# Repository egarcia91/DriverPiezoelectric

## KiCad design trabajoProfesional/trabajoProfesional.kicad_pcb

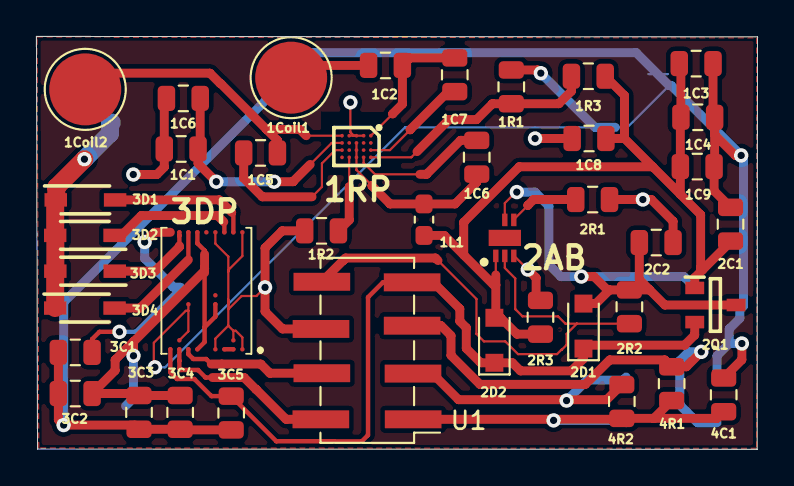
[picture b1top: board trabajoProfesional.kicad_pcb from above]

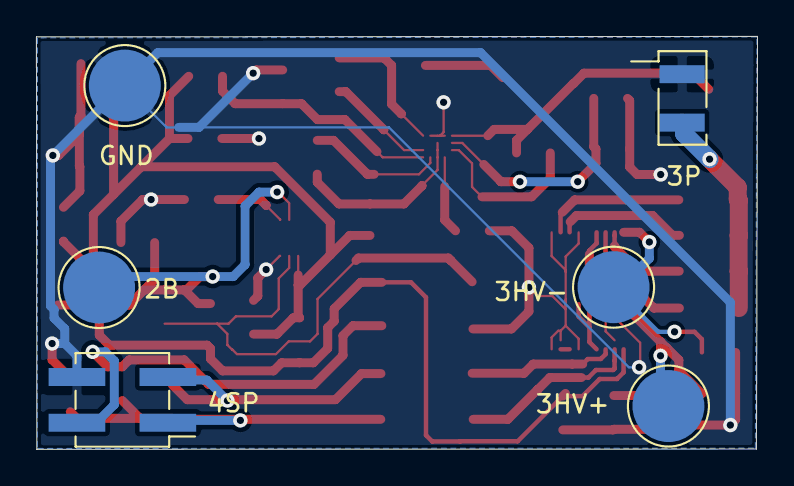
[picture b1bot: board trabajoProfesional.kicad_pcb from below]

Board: 2 copper layers, 40.1 x 22.9 mm, 46 parts (6 on the bottom side), 29 nets.

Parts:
1C1, 1C3, 1C4, 1C8, 1C9: 22u; C_0805_2012Metric
1C2: 10n; C_0805_2012Metric
1C5, 1C7: 1n; C_0805_2012Metric
1C6, 4C1: 100n; C_0805_2012Metric
1C6#2: 47n; C_0805_2012Metric
1Coil1, 1Coil2, 2B, 3HV+, 3HV-: Conn_01x01_Male; TestPoint_Pad_D4.0mm
1L1: 4.7u; L_0603_1608Metric_Pad1.05x0.95mm_HandSolder
1R1, 2R1, 2R2, 4R1, 4R2: 10k; R_0805_2012Metric
1R2: 60k; R_0805_2012Metric
1R3: 46k; R_0805_2012Metric
1RP: TS51223-M000WCSR; BGA20C40P4X5_190X230X58
2AB: SC810ULTRT; SON50P200X200X60-7N-D
2C1, 2C2: 2.2u; C_0805_2012Metric
2D1, 2D2: D_Schottky; D_SOD-323_HandSoldering
2Q1: BSS84; SOT95P240X120-3N
2R3: R; R_0805_2012Metric
3C1: 4.7; C_0805_2012Metric
3C2, 3C3, 3C4, 3C5: 4.7u; C_0805_2012Metric
3D1, 3D2, 3D3, 3D4: 1N4150W-E3-08; SOD3716X135N
3DP: HV7360GA-G; HV7360GAG
3P: UTR-1440K-TT-R; PinHeader_1x02_P2.54mm_Vertical_SMD_Pin1Left
4SP: MS583730BA01-50; PinHeader_2x02_P2.54mm_Vertical_SMD
GND: Conn_01x01_Male; TestPoint_Pad_D4.0mm
U1: 1501; PinHeader_2x04_P2.54mm_Vertical_SMD

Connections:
+Bat: 2AB.5, 2B.1, 2C2.1, 2D1.2, 2Q1.3, 2R2.1
+HV: 3C2.2, 3C3.2, 3C4.1, 3DP.A6, 3DP.F4, 3DP.P6, 3HV+.1
-HV: 3C1.2, 3DP.P9, 3HV-.1
/Bateria/Cargando: 2AB.2, 2R2.2, U1.8
/Salida/Alimentacion: 2D1.1, 2D2.1, 2Q1.2, 3C5.1, 3DP.A9, U1.1
/Salida/SN1ONOFF: 3DP.A7, U1.4
/Salida/SP1ONOFF: 3DP.A8, U1.3
GND: 1C1.1, 1C3.1, 1C4.1, 1C6.1, 1C8.1, 1C9.1, 1R1.1, 1R2.2, 1RP.B1, 1RP.C1, 1RP.D1, 2AB.3, 2C1.2, 2C2.2, 2R1.1, 2R3.1, 3C1.1, 3C2.1, 3C3.1, 3C4.2, 3C5.2, 3DP.A1, 3DP.A4, 3DP.B2, 3DP.B8, 3DP.F7, 3DP.P1, 3DP.P4, 3P.1, 4C1.1, 4SP.4, GND.1, U1.2
unnamed: 1C3.2, 1C4.2, 1C8.2, 1C9.2, 1L1.1, 1R3.1, 2AB.1, 2C1.1, 2D2.2, 2Q1.1, 2R3.2
unnamed: 2AB.4, 2R1.2
unnamed: 4C1.2, 4R1.1, 4R2.1, 4SP.1, U1.6
unnamed: 1C6#2.1, 1L1.2, 1RP.C2, 1RP.C3, 1RP.C4
unnamed: 1C6#2.2, 1RP.B4
unnamed: 1C5.1, 1RP.E3
unnamed: 1C5.2, 1Coil2.1, 1RP.E1
unnamed: 1C2.1, 1C7.1, 1RP.A1
unnamed: 1C7.2, 1RP.A3
unnamed: 1C1.2, 1C6.2, 1RP.E2
unnamed: 1C2.2, 1Coil1.1
unnamed: 3D3.1, 3DP.P8
unnamed: 3D1.1, 3D2.2, 3D3.2, 3D4.1, 3P.2
unnamed: 3D2.1, 3DP.P3
unnamed: 3D1.2, 3DP.P2
unnamed: 3D4.2, 3DP.P7
unnamed: 3DP.A2, 3DP.A3
unnamed: 1R1.2, 1R3.2, 1RP.A4
unnamed: 1R2.1, 1RP.D4
SCLPresion: 4R2.2, 4SP.3, U1.7
SDAPresion: 4R1.2, 4SP.2, U1.5

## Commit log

2020-04-02 comeinza elesquematico
2020-07-06 Se crea el primer intento de placa para el integrado dificil de soldar
2020-07-13 ahora se modifico la via para que quede lo mas grande posible y fuera del pin VGA
2020-08-16 va el parche con el ultimo mod del los pines anulados
2020-08-16 se agregan todos los componentes al squematico
2020-08-16 ya tenemos los modulos imlpementados en esquematicos, falta microprocesador
2020-08-18 ya tenemos los componentes falta el micro
2020-08-19 se agrego el Adafruit
2020-08-19 empezando el pcb
2020-08-19 paso previo PCB
2020-08-20 PCB falta una conexion
2020-08-20 va el circuito
2020-09-30 achicamiento de placa a un cuarto del tamanio anterior
2020-10-09 fue todo a doble capa con componentes de dos lados
2020-10-10 Nuevos cambios
2020-10-10 mira como ponemos todo de una cara
2020-10-13 componentes en una capa
2020-10-13 doble capa incluyendo el modelo 3D
2020-10-20 se hacen mas gruesas las pistas y se rellena el area sin uso de la parte frontal
2020-11-11 va lo actual
2020-11-17 se agregan los nuevos tamanios de componentes
2021-01-11 Ultima placa que imprimimos todo junto
2021-01-12 Va las nuevas placas modulares, faltan interconexion entre modulos y planos
2021-01-13 Placa uno terminada!
2021-01-14 cuatro placas listas
2021-01-15 agregamos los dos circuitos que nos faltaban, cargador y centralizador
2021-01-19 el paso previo a agregar todos los componentes de las otras placas
2021-01-19 nos topamos con un footprint que no coincide (TS80002)
2021-01-19 placa numero cinco, nos falta cambiarle los nombres a los componentes de vuelta
2021-02-25 se modifica el componente que no tenemos
2021-03-02 Editado el footprint que no teniamos, completando las ultimas placas
2021-03-07 "placa 6 casi completa"
2021-03-08 Se completo el centralizador, falta el step-up
2021-03-09 antes de que explote la bomba, agregamos la ultima placa de stepup stepdown
2021-03-09 se agregan las relaciones de footprints a los nuevos componentes
2021-03-09 terminadas las 8 placas modulares. Para mandar a imprimir!
2021-03-11 se unifica todo
2021-03-12 se agregan lineas
2021-03-12 Ultimas modificaciones de las lineas
2021-03-12 Revert "Ultimas modificaciones de las lineas"
    se vuelve al estado anterior!
    This reverts commit 6775e72ca7e72ceb68c45e191fec203a9774ccb5.
2021-03-12 se mueven dos lineas
2021-06-20 modelos 3d modulares
2021-07-02 sera la placa final?
